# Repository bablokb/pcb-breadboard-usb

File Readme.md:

Simple PCB for a breadboard power-supply using a Micro-USB connector and a AMS1117 breakout
===========================================================================================

This is a simple power-supply for a breadboard. There are ready to use power-supplies for
breadboards available, but you usually need a barrel-plug for them and the quality is
not the best. In addition, using a micro-usb connector allows to add data-connections as
well.

The stripboard-design uses a standard micro-usb breakout and an AMS1117 breakout for
the regulator (on the left). The breakout already has the necessary capacitors.

Note that on most breadboards the power and ground row are offset a bit from the normal
pins, so it is not possible to use a stripboard and plug into the power/ground rows directly.

The layout is simple, you only have to provide two wires in addition to the breakouts:

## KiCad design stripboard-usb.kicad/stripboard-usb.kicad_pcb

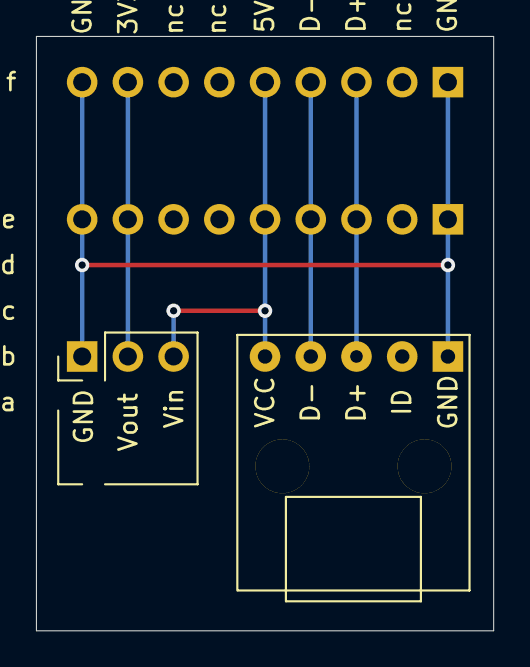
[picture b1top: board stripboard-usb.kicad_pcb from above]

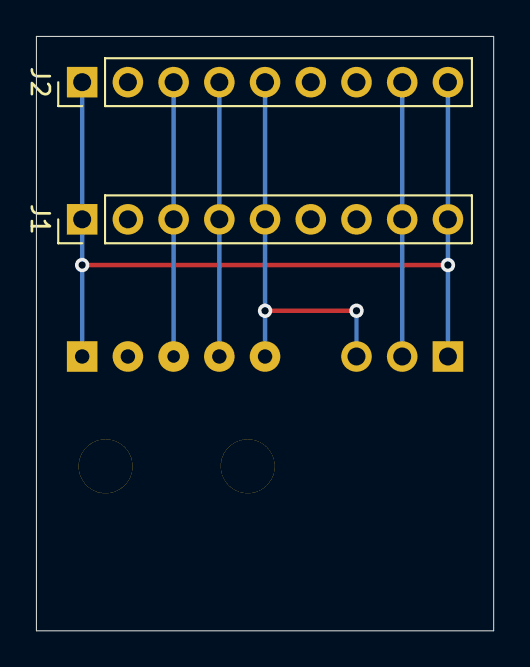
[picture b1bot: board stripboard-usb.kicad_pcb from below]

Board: 2 copper layers, 25.4 x 33.0 mm, 4 parts (2 on the bottom side), 5 nets.

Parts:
J1, J2: Conn_01x09_Male; PinHeader_1x09_P2.54mm_Vertical
U1: AMS1117; AMS1117_Breakout
USB1: Micro-USB_Breakout

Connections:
unnamed: J1.1, J1.9, J2.1, J2.9, U1.1, USB1.1
unnamed: J1.3, J2.3, USB1.3
unnamed: J1.4, J2.4, USB1.4
unnamed: J1.5, J2.5, U1.3, USB1.5
unnamed: J1.8, J2.8, U1.2

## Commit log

2020-07-02 reduces size
